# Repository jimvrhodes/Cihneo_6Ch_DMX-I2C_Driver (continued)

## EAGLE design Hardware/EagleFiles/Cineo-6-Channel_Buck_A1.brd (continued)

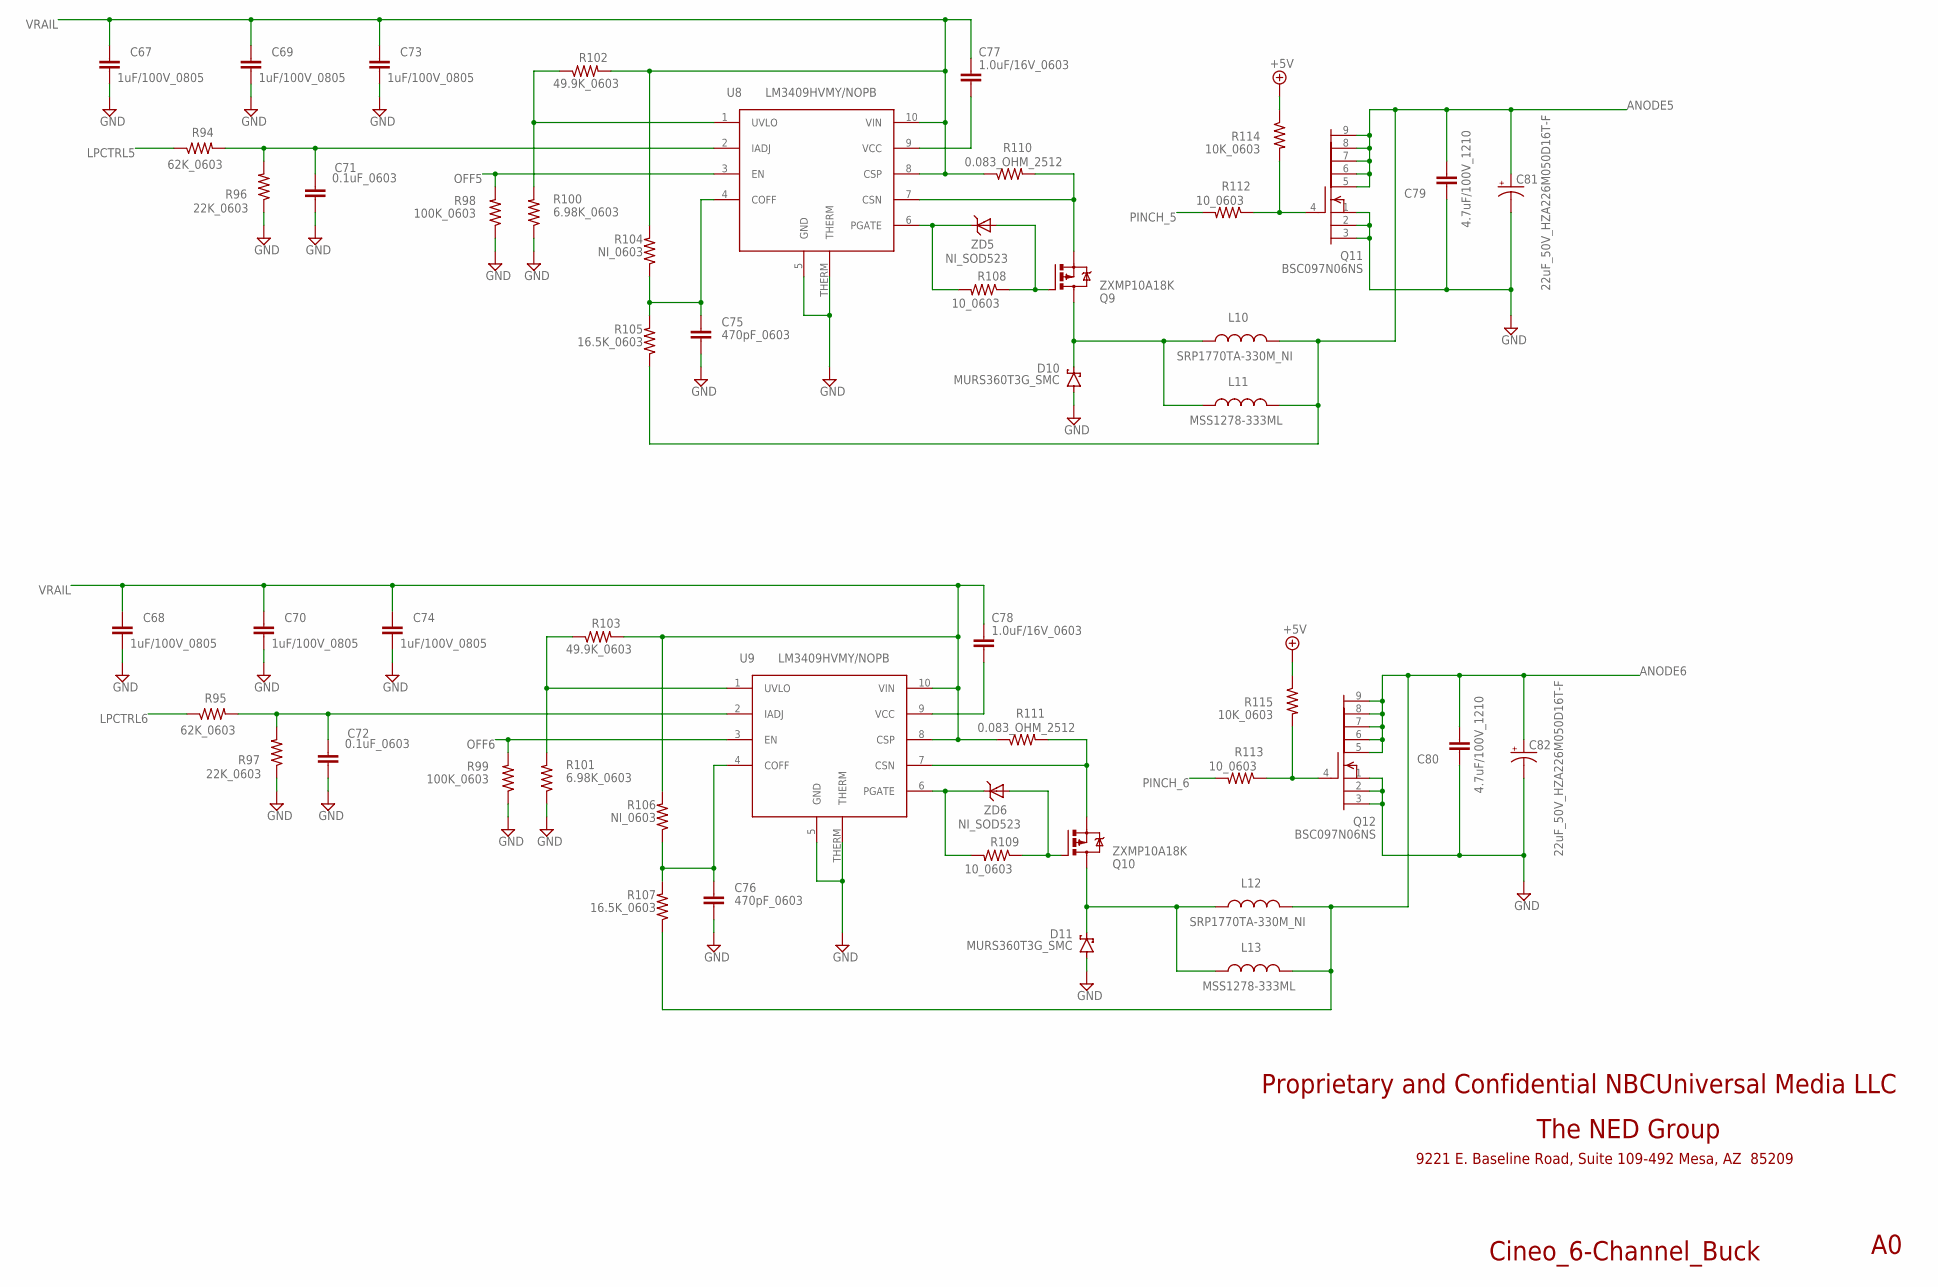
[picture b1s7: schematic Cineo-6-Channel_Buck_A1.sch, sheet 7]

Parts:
C67, C68, C69, C70, C73, C74: 1uF/100V_0805; C0805
C71, C72: 0.1uF_0603; C0603
C75, C76: 470pF_0603; C0603
C77, C78: 1.0uF/16V_0603; C0603
C79, C80: 4.7uF/100V_1210; C1210
C81, C82: 22uF_50V_HZA226M050D16T-F; PANASONIC_D
D10, D11: MURS360T3G_SMC; SMC
L10, L12: SRP1770TA-330M_NI; BOURNS_SRP1770TA
L11, L13: MSS1278-333ML; MSS1260
Q9, Q10: ZXMP10A18K; DPAK
Q11, Q12: BSC097N06NS; SO-8_POWERPAC
R94, R95: 62K_0603; R0603
R96, R97: 22K_0603; R0603
R98, R99: 100K_0603; R0603
R100, R101: 6.98K_0603; R0603
R102, R103: 49.9K_0603; R0603
R104, R106: NI_0603; R0603
R105, R107: 16.5K_0603; R0603
R108, R109, R112, R113: 10_0603; R0603
R110, R111: 0.083_OHM_2512; R2512
R114, R115: 10K_0603; R0603
U8, U9: LM3409HVMY/NOPB; MSOP10-THERMALENHANCED
ZD5, ZD6: NI_SOD523; SOD-523

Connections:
+5V: R114.1, R115.1; also elsewhere on the board
ANODE5: C79.2, C81.+, L10.P$2 (2), L11.2, Q11.5 (D), Q11.6 (D1), Q11.7 (D2), Q11.8 (D3), Q11.9 (D4), R105.1; also elsewhere on the board
ANODE6: C80.2, C82.+, L12.P$2 (2), L13.2, Q12.5 (D), Q12.6 (D1), Q12.7 (D2), Q12.8 (D3), Q12.9 (D4), R107.1; also elsewhere on the board
GND: C67.2, C68.2, C69.2, C70.2, C71.1, C72.1, C73.2, C74.2, C75.1, C76.1, C79.1, C80.1, C81.-, C82.-, D10.A, D11.A, Q11.1 (S), Q11.2 (S1), Q11.3 (S2), Q12.1 (S), Q12.2 (S1), Q12.3 (S2), R96.1, R97.1, R98.1, R99.1, R100.1, R101.1, U8.5 (GND), U8.THERM, U9.5 (GND), U9.THERM; also elsewhere on the board
LPCTRL5: R94.1; also elsewhere on the board
LPCTRL6: R95.1; also elsewhere on the board
unnamed: R100.2, R102.1, U8.1 (UVLO)
unnamed: C71.2, R94.2, R96.2, U8.2 (IADJ)
unnamed: Q11.4 (G), R112.1, R114.2
unnamed: C75.2, R104.1, R105.2, U8.4 (COFF)
unnamed: C77.1, U8.9 (VCC)
unnamed: Q9.E (S), R110.2, U8.7 (CSN)
unnamed: Q9.B (G), R108.1, ZD5.A
unnamed: R108.2, U8.6 (PGATE), ZD5.C
unnamed: D10.C, L10.P$1 (1), L11.1, Q9.C (D)
unnamed: R101.2, R103.1, U9.1 (UVLO)
unnamed: C72.2, R95.2, R97.2, U9.2 (IADJ)
unnamed: Q12.4 (G), R113.1, R115.2
unnamed: C76.2, R106.1, R107.2, U9.4 (COFF)
unnamed: C78.1, U9.9 (VCC)
unnamed: Q10.E (S), R111.2, U9.7 (CSN)
unnamed: Q10.B (G), R109.1, ZD6.A
unnamed: R109.2, U9.6 (PGATE), ZD6.C
unnamed: D11.C, L12.P$1 (1), L13.1, Q10.C (D)
OFF5: R98.2, U8.3 (EN); also elsewhere on the board
OFF6: R99.2, U9.3 (EN); also elsewhere on the board
PINCH_5: R112.2; also elsewhere on the board
PINCH_6: R113.2; also elsewhere on the board
VRAIL: C67.1, C68.1, C69.1, C70.1, C73.1, C74.1, C77.2, C78.2, R102.2, R103.2, R104.2, R106.2, R110.1, R111.1, U8.8 (CSP), U8.10 (VIN), U9.8 (CSP), U9.10 (VIN); also elsewhere on the board

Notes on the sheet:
Cineo_6-Channel_Buck
The NED Group
9221 E. Baseline Road, Suite 109-492 Mesa, AZ 85209
Proprietary and Confidential NBCUniversal Media LLC

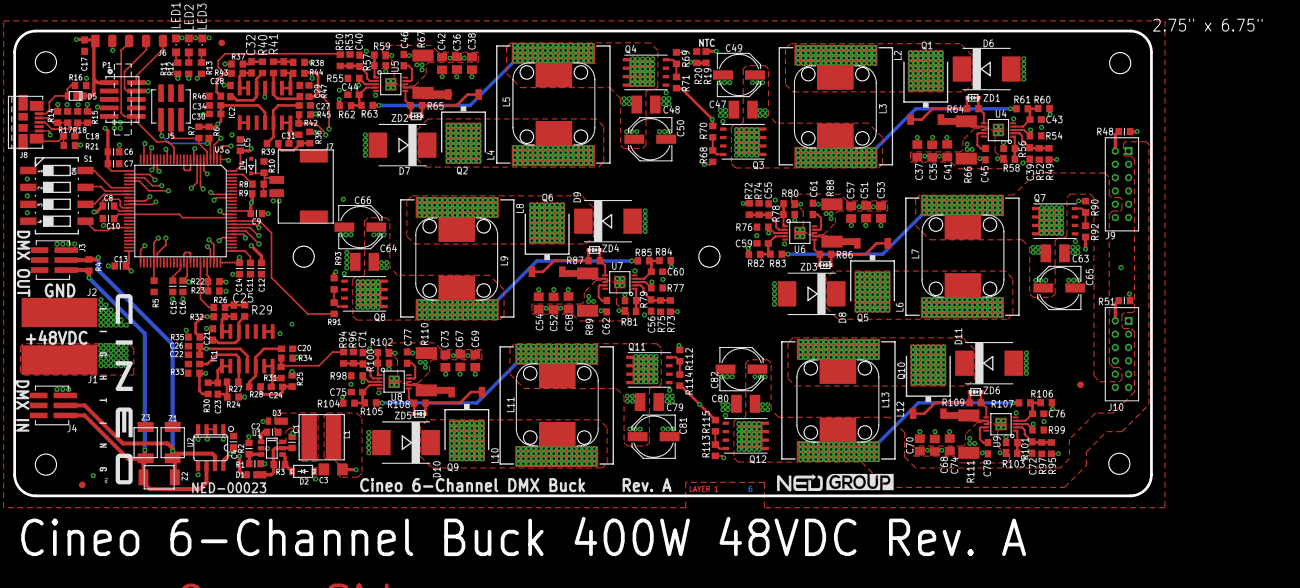
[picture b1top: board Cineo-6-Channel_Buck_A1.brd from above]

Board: 6 copper layers, 190.9 x 83.9 mm, 272 parts (0 on the bottom side), 149 nets.

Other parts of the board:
DRILEGEND: DRILEGEND

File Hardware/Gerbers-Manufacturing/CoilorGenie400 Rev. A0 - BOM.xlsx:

Item | Qty | P/N | Title | Detail | Reference(m) | Cur/Assy/MFCost
1 | 1 | CAP-00159 | Capacitor, 0.15uF, 50V, Non-Polar, X7R, Ceramic, 10%, 0603 | C0603C154K5RACAUTO | C2 | 7.6999999999999999E-2 | 7.6999999999999999E-2
2 | 25 | CAP-00240 | Capacitor, 0.1uF, 100V, Non-Polar, X7R, Ceramic, 10%, 0603 | HMK107B7104KA-T | C1, C4, C5, C7, C8, C9, C13, C14, C16, C17, C18, C19, C20, C21, C22, C27, C28, 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 | 4.2000000000000003E-2 | 1.05
3 | 6 | CAP-00051 | Capacitor, 0.22uF, 16V, Non-Polar, X7R, Ceramic, 0603, SMT | VJ0603Y224KXJCW1BC | C23, C24, C25, C31, C32, C33 | 2.4E-2 | 0.14400000000000002
4 | 20 | CAP-00188 | Capacitor, 1uF, 100V, Non-Polar, X7S, Ceramic, 20%, 0805 | C2012X7S2A105M125AE | C26, C34, C35, C36, C37, C38, C41, C42, C51, C52, C53, C54, C57, C58, C67, C68,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 | 0.14399999999999999 | 2.88
5 | 11 | CAP-00131 | Capacitor, 1uF, 50V, Non-Polar, X7R, Ceramic, 10%, 0603 | UMK107BJ105KA-T | C6, C10, C11, C12, C15, C45, C46, C61, C62, C77, C78 | 6.9000000000000006E-2 | 0.75900000000000012
6 | 6 | CAP-00189 | Capacitor, 22uF, 50V, Electro, Alum, 20%, 105C, 6.6mm x 6.6mm SMD 6.1mm Tall | HZA226M050D16T-F | C49, C50, C65, C66, C81, C82 | 0.87 | 5.22
7 | 6 | CAP-00149 | Capacitor, 4.7uF, 100V, Non-Polar, X7S, Ceramic, 20%, 1210 | CGA6M3X7S2A475K200AB | C47, C48, C63, C64, C79, C80 | 0.5 | 3
8 | 6 | CAP-00098 | Capacitor, 470pF, 50V, Non-Polar, Ceramic, 10%, 0603 | C0603C471K5RAC | C43, C44, C59, C60, C75, C76 | 2.5000000000000001E-2 | 0.15000000000000002
9 | 1 | CAP-00301 | Capacitor, 47uF, 10V, Non-Polar, X5R, 1206, 20% | C1206C476M8PACTU | C3 | 0.56899999999999995 | 0.56899999999999995
10 | 1 | CONN-00058 | Connector, 10-Pos, 2-Row, 1.27mm, DIL Vert Pin Head, SMT | M50-3600542R | P1 | 1.25 | 1.25
11 | 2 | CONN-00116 | Connector, 1-Pos, 3mm, Poke-Home, 20A/300V, RA, SMT | 709296001004006 | J1, J2 | 0.249 | 0.498
12 | 2 | CONN-00084 | Connector, JST, 2mm, IDC 22 gague wire use, 3A, 250V, 12-pos, TH | B12B-PHDSS(LF)(SN) | J9, J10 | 0.47299999999999998 | 0.94599999999999995
13 | 1 | CONN-00110 | Connector, Molex, DuraClik, 2-Pos, Locking, Tin, 2mm, Vertical, White, SMT | 560020-0220 | J7 | 0.51300000000000001 | 0.51300000000000001
14 | 3 | CONN-00111 | Connector, Molex, Pico-SPOX, 3-Pos, Locking, Tin, 1/5mm, Vertical, White, SMT | 874370343 | J3, J4, J5 | 0.53200000000000003 | 1.5960000000000001
15 | 1 | CONN-00062 | Connector, USB micro, Female, RA, PCB Mount, SMT | 47346-1001 | J8 | 0.63 | 0.63
16 | 6 | DIODE-00048 | Diode, Rectifier, 600V, 3A, SMC, SMT | MURS360T3G | D6, D7, D8, D9, D10, D11 | 0.45 | 2.7
17 | 3 | DIODE-00001 | Diode, Schottky, Barrier, 60V, 1A, TUMD2 | RB160VYM-60FHTR | D1, D3, D5 | 0.1 | 0.30000000000000004
18 | 1 | DIODE-00115 | Diode, Zener, 3.3V, 200mW, 2%, SOD-323 | MM3Z5V1B | D4 | 5.8999999999999997E-2 | 5.8999999999999997E-2
19 | 1 | DIODE-00111 | Diode, Zener, 3.3V, 500mW, 2%, SOD-123 | BZT52C3V3-E3-18 | D2 | 9.0999999999999998E-2 | 9.0999999999999998E-2
20 | 1 | IC-00060 | IC, Analog Devices RS-485 Transceiver, 500kbs, 3-5.5VDC, +/-12kV Isolation, 1/8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 | ADM3061EARZ | U2 | 2.09 | 2.09
21 | 1 | IC-00061 | IC, Cypress PSoC5, ARM M3, 256K Flash, 64K SRAM, 100-TQFP | CY8C5287AXI-LP095 | U3 | 5 | 5
22 | 6 | IC-00078 | IC, LM3409HV, Buck LED Driver, High Side CS, 6V to 75V Input, 5A, MSOP-PowerPad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 | LM3409HVMY/NOPB | U4, U5, U6, U7, U8, U9 | 0.83599999999999997 | 5.016
23 | 1 | IC-00048 | IC, MP2459GJ, Buck, Power Controller, 5V-55V, 600mA, TSOT23-6 | MP2459GJ-Z | U1 | 0.88200000000000001 | 0.88200000000000001
24 | 2 | IC-00062 | IC,4-Circuit Op-Amp, 1.8-5.5VDC, Rail-to-Rail, SOIC-14 | MCP6424T-E/SL | IC1, IC2 | 0.78300000000000003 | 1.5660000000000001
25 | 1 | INDUCTOR-00111 | Inductor, SMT, Power, 15uH, 0.095 DCR, 40 SRF, 1.3A Isat, 0.90 Irms, 2.4mm tall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 | LPS6225-153MRC | L1 | 1.22 | 1.22
26 | 6 | INDUCTOR-00015 | Inductor, SMT, Power, 47uH, 73 DCR, 80 SRF, 4.76A Isat, 2.00 Irms, 7.8mm tall x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 | MSS1278-473MLB | L3, L5, L7, L9, L11, L13 | 0.5 | 3
27 | 1 | LED-00004 | LED, Blue, Indicator, Water Clear, 0805 | LTST-C170TBKT | LED1 | 0.2 | 0.2
28 | 1 | LED-00001 | LED, Green, Indicator, Water Clear, 0805 | CMD17-21VGC/TR8 | LED3 | 0.14000000000000001 | 0.14000000000000001
29 | 1 | LED-00002 | LED, Red, Indicator, Water Clear, 0805 | 150080RS75000 | LED2 | 0.16 | 0.16
30 | 6 | FET-00031 | MOSFET, N-Channel, OptiMOS3, 60V, 46A, 9.7mOhm, Logic Gate, TDSON-8 | BSC097N06NSATMA1 | Q3, Q4, Q7, Q8, Q11, Q12 | 0.53800000000000003 | 3.2280000000000002
31 | 6 | FET-00037 | MOSFET, P-Channel, 159mOhms, 100V, 5.9A, TO-252-3 | ZXMP10A18KTC | Q1, Q2, Q5, Q6, Q9, Q10 | 0.86 | 5.16
32 | 1 | PCB-NED-00023-A | PCB, NED, ColorGenie400, 6-Layer, 2.75" x 6.75", FR4 |  |  | 5 | 5
33 | 6 | RES-00613 | Resistor, 0.083-ohm, 3W, 2512, 1%, Thick Film | CRA2512-FZ-R080ELF | R66, R67, R88, R89, R110, R111 | 0.22500000000000001 | 1.35
34 | 6 | RES-00063 | Resistor, 0-ohm, 1/8W, 1%, 0603, Thick Film | RC0603JR-070RL | R30, R31, R32, R42, R43, R44 | 1.4999999999999999E-2 | 0.09
35 | 10 | RES-00561 | Resistor, 100K, 1/10W, 0603, 1%, Thick Film | RC0603FR-07100KL | R3, R5, R21, R22, R54, R55, R76, R77, R98, R99 | 3.0000000000000001E-3 | 0.03
36 | 11 | RES-00559 | Resistor, 10K, 1/10W, 0603, 1%, Thick Film | RC0603FR-0710KL | R6, R7, R19, R48, R51, R70, R71, R92, R93, R114, R115 | 3.0000000000000001E-3 | 3.3000000000000002E-2
37 | 12 | RES-00153 | Resistor, 10-ohm, 1/10W, 1%, 100PPM, 0603, Thick Film | RC0603FR-0710RP | R64, R65, R68, R69, R86, R87, R90, R91, R108, R109, R112, R113 | 1.2999999999999999E-2 | 0.156
38 | 1 | RES-00031 | Resistor, 15K, 1/10W, 1%, +/-100PPM, 0603, Thick Film | RC0603FR-0715KL | R9 | 6.0000000000000001E-3 | 6.0000000000000001E-3
39 | 6 | RES-00193 | Resistor, 16.5K, 1/10W, 0603, Thick Film | RC0603FR-0716K5L | R61, R63, R83, R85, R105, R107 | 4.0000000000000001E-3 | 2.4E-2
40 | 4 | RES-00560 | Resistor, 1K, 1/10W, 0603, 1%, Thick Film | RC0603FR-071KL | R2, R11, R12, R13 | 3.0000000000000001E-3 | 1.2E-2
41 | 18 | RES-00163 | Resistor, 22K, 1/10W, 0603, 1%, Thick Film | _x000D_ RC0603FR-0722KL | R24, R25, R26, R27, R28, R29, R36, R37, R38, R39, R40, R41, R52, R53, R74, R75,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 | 6.0000000000000001E-3 | 0.108
42 | 2 | RES-00308 | Resistor, 22-Ohm, 1/10W, 0603, 1%, Thick Film | RC0603FR-0722RL | R14, R15 | 0.01 | 0.02
43 | 6 | RES-00247 | Resistor, 31.6K, 1/10W, 1%, +/-100PPM, 0603, Thick Film | RC0603FR-0731K6L | R49, R50, R72, R73, R94, R95 | 6.0000000000000001E-3 | 3.6000000000000004E-2
44 | 6 | RES-00105 | Resistor, 49.9K, 1/10W, 0603, 1%, 100PPM, Thick Film | RC0603FR-0749K9L | R58, R59, R80, R81, R102, R103 | 6.0000000000000001E-3 | 3.6000000000000004E-2
45 | 1 | RES-00263 | Resistor, 5.11K, 1/10W, 0603, Thick Film | RC0603FR-075K11L | R1 | 6.0000000000000001E-3 | 6.0000000000000001E-3
46 | 1 | RES-00575 | Resistor, 510-ohm, 1/10W, 0603, 1%, Thick Film | RC0603FR-07510RL | R8 | 6.0000000000000001E-3 | 6.0000000000000001E-3
47 | 7 | RES-00205 | Resistor, 68K, 1/10W, 0603, 1%, Thick Film | RC0603JR-0768KL | R23, R56, R57, R78, R79, R100, R101 | 6.0000000000000001E-3 | 4.2000000000000003E-2
48 | 1 | SWITCH-00007 | Switch, 4-DIP, SPST, 100mA, 50V, Top Slide, 4-Pos, 0.100:, SMT | 219-4MST | S1 | 0.63 | 0.63
49 | 1 | THERMISTOR-00001 | Thermistor, NTC, 10K, 0603, Curve 2, 5% | NCP18XH103J03 | R20 | 6.6000000000000003E-2 | 6.6000000000000003E-2
50 | 3 | TRANSORB-00014 | Transorb, 13.3 V to 15.3 V, 1A, Bidirectional, SMBJ (DO-214AA), J-Bend, SMT | SMBJ12CA | Z1, Z2, Z3 | 0.19700000000000001 | 0.59099999999999997
51 | 3 | TRANSORB-00011 | Transorb, 5V, 100A, Static, SMT, 0603 | CG0603MLC-05LE | R16, R17, R18 | 0.01 | 0.03
 |  |  |  |  |  | Total | 58.366000000000028

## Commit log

2020-05-03 Rev A file to repo
